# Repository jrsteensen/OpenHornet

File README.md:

# README
[TOC]

The OpenHornet Project is a F/A-18C OFP 13C Lot 20 1:1 Replica Simulator, consisting of a physical structure and electrical/software interfaces to a PC to be driven by Digital Combat Simulator (DCS).

* If you have any questions, visit our Discord server and ask questions. The Discord server will be an invaluable resource for you as your progress through the journey of your build.

### Looking for Software?
* [OpenHornet GitHub Software Repository](https://github.com/jrsteensen/OpenHornet-Software)

## Design Software Requirements
* Mechanical CAD Software Required: Fusion360
* Electrical CAD Software Required: KiCad 10
* Microsoft Office (or compatible)

## Contributing
[Want to contribute?](https://github.com/jrsteensen/OpenHornet/wiki/Contributing) Let's discuss what you want to work on in Discord or in an issue!

## References, Information, and How-Tos

### GitHub Repository File Structure
```
OpenHornet
├── .github (Contains issue templates, funding info, and GitHub actions.)
├── artwork (Subdivided into end items, contains stickers, placards, etc.)
├── ECAD (All PCBs and electrical design files. See folder README file for details.)
├── images (Contains images for use in the wiki or other OH documentation.)
├── reference (Contains reference models or geometry.)
├── release (Contains all files that makeup the release package. See folder README file for details.)
├── utils (Contains fonts or other similar required resources for development)
├── .gitignore (File that instructs the git repository to ignore certain file types.)
├── CODE_OF_CONDUCT.md (Our contributor code of conduct.)
├── CONTRIBUTING.md (Repository contribution and issue-reporting guidance.)
├── LICENSE.md (License file for the OpenHornet repository)
├── PULL_REQUEST_TEMPLATE.md (The repository pull request template.)
└── README.md (This file)
```

### Important Links
* [OpenHornet Start Here Page](https://openhornet.com/start-here/) - Seriously. Start here.
* [OpenHornet FAQ](https://openhornet.com/faq/) - You guessed it! The FAQ!
* [OpenHornet GitHub](https://github.com/jrsteensen/OpenHornet) - OpenHornet's GitHub repository for everything other than MCAD. Where you can find the latest under-development files.
* [OpenHornet Hardware Documentation](https://docs.openhornet.com/hardware/) - Generated hardware documentation, tutorials, and reference material.
* [OpenHornet Tutorials](https://github.com/jrsteensen/OpenHornet/tree/master/docs/tutorials) - Tutorials for OpenHornet.
* [OpenHornet Issues](https://github.com/jrsteensen/OpenHornet/issues) - Go here to file a bug, enhancement, obsolescence, or maintenance issue.
* [OpenHornet Authorized Vendors](https://openhornet.com/openhornet-authorized-vendors/) - These are vendors who are licensed to sell OpenHornet parts and assemblies. By purchasing from them, you also support OpenHornet as well!

### OpenHornet MCAD Model
These links will allow you to download a local copy of the OH MCAD model, for reference or so you can modify things for your personal pit. If you would like to contribute to the raw MCAD, talk to Noctum in the OH Discord. You will need to prove a basic level of proficiency and be known within the discord community before access will be granted.
> [!NOTE] 
> These links will download the latest & greatest (most likely in development and unstable) MCAD. Always verify fusion parts against release package manufacturing files prior to use, and they are used at the user's own risk.

* [Top Level](https://a360.co/3SuPQGs) - This is HUGE. Consider downloading individual consoles instead.
* [Upper Instrument Panel (UIP)](https://a360.co/3LHxMXd)
* [Lower Instrument Panel (LIP)](https://a360.co/3SbD7sc)
* [Left Console (LC)](https://a360.co/3dBR57I)
* [Right Console (RC)](https://a360.co/37pBiWj)
* [Center Tub (CT)](https://a360.co/3LKM3mc)

### Branches
* `master` branch is the stable release branch which represents the last release.
* `develop` is the latest working branch that will become the next release. It may or may not be functional as is.

## Authors and Acknowledgment

### Core Development Team
* Erik Scott (RandomTroubledMind): _Project Founder, Mechanical Design_ (Retired from OH)
* John Steensen (Noctum): _Co-Founder, Systems/Mechanical Design Lead_
* Oscar Arias (Amanuense): _Electrical/Software Design Lead_ (Retired from OH)

### Contributor Team
* Exprezzo
* Sandra
* Ben-F111
* Lazarus
* Russell
* Arribe VCAW-1
* Stang
* \[OCS\] CrazyCanuck
* Ulikaii

### Honorable Mentions
* __Logo Design__: NegativeONE
* __Development Builders/Testers__: Ajmilner,  Arribe VCAW-1, Ben-F111, BlaBlaCZ, bnepethomas, Dave the boss 918, DG, DotDotDotBH, Exprezzo, Higgins, Krikeee, Lazarus, Otso, Rampage2010, Russell, Sandra, Splash, Thib-O, tonyg, TripRodriguez, Yannick, 
* __Ultimate Supporters__: Sandra, Higgins, Chaps, [OCS] CrazyCanuck, Arribe VCAW-1, FL370Pilot, CorgiStyle, Swaney409, DenzilLee, ssgcline, Tyler | "Soapbox" - F-15E, RickH, AdamA, bob =), aesellars, Nick, PrivatePirate, Howling-Ape, papiplanes
* __Elite Supporters__: thib_o54, ChrisTiger#001, Nodar, Matt, Bill C, annerajb, Wargle T Eagle, Gnoni, Lefty, Reaper021, Murtle, gengispala, PatOPat, mattgw86, EinLama, Maddox, hunstone, Nodar, Ulukaii, Radek 41Sqn RAFAIR, mojito555
* __Donators__: AJMilner, bnepethomas, Carbine, Crosshairs, Exprezzo, Goutch, Higgins, hrnet940, hunstone, icemarkom, jcstreek, jkkicks, kika, Nik S, Rampage2010, Russell, Sandra, SrSosio, Swaney409, Tekadept + many more…
* __Inactive Dev Contributors__: Balz Reber (Balse), Magic_Man, Bullant, Gaberun24, Damien022, Baago, Caviar4, NegativeONE, Ravell
* **Subject Matter Expert**: FlyNavy75, Sixtigers, USMARINE108, Luft101, Lex

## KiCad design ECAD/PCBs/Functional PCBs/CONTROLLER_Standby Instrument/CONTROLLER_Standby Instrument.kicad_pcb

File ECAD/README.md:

* [OpenHornet Website](https://www.openhornet.com)
* [OpenHornet Discord](https://discord.gg/G5PA5ju)
* [Donate to OpenHornet](https://www.openhornet.com/donate.html)

# **ECAD DIRECTORY INFORMATION**

Engineering contributors and agents: start with the [ECAD design requirements framework](docs/requirements/README.md). AI-assisted contributors should also read the [Astra/Konnect/KiCad toolchain guide](docs/requirements/TOOLCHAIN.md). The framework distinguishes repository evidence, approved policy, unresolved decisions and hardware qualification states.

The purpose of this guide is to help enable the end-user to successfully accomplish the following:  
*   1:  Facilitate navigation of the file structure.
*   2:  Provide clarification regarding the manufacturing process of PCB's related to OpenHornet using JLCPCB.com
*   3:  How to install the current project KiCad baseline and set up libraries associated with OpenHornet. _(optional, required only if you wish to contribute.)_

 _Note:  Manufacturing files have been generated accordinging to JLCPCB.com guidelines.  If choosing a different PCB Manufacturer, make sure to research their formatting standards and modify the necessary manufacturing files accordingly. And if you choose to manufacture them yourself, best of luck!_

## **ECAD File Structure**

The ECAD Directory has been organized to facilitate the end user, regardless of skill or knowledge, in acquiring the necessary files needed to: 
* A: make adjustments to individual PCB's as needed using ECAD software (KiCad)
     * _and/or_
* B: submit an online order to have the PCB manufactured and assembled by a company.

**The structure of the ECAD Directory is summarized below:**

1. Within each labeled PCB folder, there will be a folder called "JLCPCB" and inside of that folder will be two additional folders called "gerbers" and "production_files"
2. **_All files you need for manufacturing are located in the "production_files" folder.  The gerbers are already compressed in a .zip file labeled the same way as the PCB folder their located in._** 
3. Additionally, there will be 2 .csv files:  _**BOM-'NAME OF PANEL'.csv**_ and  _**CPL-'NAME OF PANEL'.csv**_ that will contain a consolidated Bill of Materials (BOM) for components located on the top and bottom of the PCB, as well as the Control Panel File (CPL)  used for placing the components.

***PLEASE READ:  YOU NEED TO DOWNLOAD ALL 3 FILES WITHIN THE PRODUCTION_FILES FOLDER.  NOT JUST THE .ZIP.***

## **PCB Manufacturing**

At the moment, all manufacturing files have been standardized to allow for fabrication using JLC @ (https://www.jlcpcb.com).  You may use another PCB manufacturer of your choosing; however, you will be responsible for ensuring the required files meet specifications and formatting. 

***For details on the JLCPCB manufacturing process, please see the "MANUFACTURING.MD" located in the ECAD folder or CLICK THE LINK BELOW***

  [JLCPCB MANUFACTURING PROCESS & FAQ](MANUFACTURING.md)

## **Installation of KiCad and OpenHornet Libraries _(OPTIONAL)_**

*Installation of KiCad and OpenHornet Libraries is only required if you choose to contribute. See [CONTRIBUTING.md](../CONTRIBUTING.md) for more details.*

Before we begin, it is assumed that you have:
*  1:  Installed KiCad 10.x. The current validated AI-assisted reference environment uses KiCad 10.0.6; record and smoke-test newer versions before design mutation as described in [TOOLCHAIN.md](docs/requirements/TOOLCHAIN.md).
*  2:  Cloned the OpenHornet repository.

### STEP ONE:  Configure Paths & Create Environmental Variables

**Windows shortcut:** initialize KiCad 10 with its built-in libraries, then close KiCad and double-click [`Setup-OpenHornetKiCad.bat`](../utils/tools/ecad/Setup-OpenHornetKiCad.bat). The [complete setup script](docs/SYMBOL_LIBRARIES.md#windows-path-setup-script) configures all four paths, registers all six shared symbol libraries and `OH_Footprints`, and repairs existing shared entries in project library tables. It backs up every changed file and supports a preview with `-WhatIf`. After it succeeds, reopen KiCad; Steps One and Two below are the manual alternative.

Open up a new or previous project in KiCad.  For this example, I'll be using the MASTER ARM PANEL.  In the Top Menu: Navigate to Preferences --> Configure Paths

Create these four variables using absolute paths within your OpenHornet checkout:

| Variable | Repository folder |
| --- | --- |
| `KICAD_USER_OH_3DMODELS` | `ECAD/lib/OH_3DModels` |
| `KICAD_USER_OH_FOOTPRINTS` | `ECAD/lib` |
| `KICAD_USER_OH_SYMBOLS` | `ECAD/lib/OH_Symbols` |
| `KICAD_USER_OH_TEMPLATES` | `ECAD/lib/OH_Templates` |

The paths can be anywhere so long as they point to the OpenHornet checkout being edited. _Make sure the OH_FOOTPRINTS variable points to the `ECAD/lib` folder and **NOT** `ECAD/lib/OH_Footprints.pretty`._ If you use Git worktrees, do not let KiCad resolve libraries from a different checkout/revision than the PCB or schematic being edited.

### STEP TWO:  Add OpenHornet Symbol and Footprint Libraries

With the project window open, navigate to Preferences --> Manage Symbol Libraries.

In **Global Libraries**, add or edit the six shared libraries below. Use library format **KiCad** for each entry. The library paths use the variable configured above:

| Nickname | Library Path |
| --- | --- |
| `ABSIS` | `${KICAD_USER_OH_SYMBOLS}/ABSIS.kicad_sym` |
| `Arduino Pro Mini 5v` | `${KICAD_USER_OH_SYMBOLS}/Arduino Pro Mini 5v.kicad_sym` |
| `KiCadCustomLib` | `${KICAD_USER_OH_SYMBOLS}/KiCadCustomLib.kicad_symdir` |
| `OH_Interconnect` | `${KICAD_USER_OH_SYMBOLS}/OH_Interconnect.kicad_symdir` |
| `OH_Symbols` | `${KICAD_USER_OH_SYMBOLS}/OH_Symbols.kicad_symdir` |
| `OpenHornet` | `${KICAD_USER_OH_SYMBOLS}/OpenHornet.kicad_symdir` |

**Existing users:** change the paths for `OH_Symbols`, `KiCadCustomLib`, `OH_Interconnect` and `OpenHornet` from packed `.kicad_sym` files to their `.kicad_symdir` folders, using the exact nicknames in the table. Register each folder as one library, rather than adding its individual files. Check **Project Specific Libraries** for overriding entries with the same nicknames. `ABSIS` and `Arduino Pro Mini 5v` remain packed files.

Use the exact underscore nicknames `OH_Symbols` and `OH_Interconnect`, as shown in the table; do not substitute spaces. If a schematic still contains a library ID using a spaced nickname, correct its library reference through KiCad's symbol remapping tools. Changing a library-table nickname alone does not rewrite IDs embedded in schematics.

See [symbol library setup, Windows conversion and verification](docs/SYMBOL_LIBRARIES.md). Contributors pulling the converted folder only need to update their library mapping. The screenshots below illustrate the dialogs; use the paths in this table for KiCad 10.

Do the same thing for the footprint library, adding `ECAD/lib/OH_Footprints.pretty` with nickname `OH_Footprints`. The path should resolve as `${KICAD_USER_OH_FOOTPRINTS}/OH_Footprints.pretty`.

### STEP THREE:  Add ***KiCAD JLCPCB tools*** Plugin (Optional)
Bouni @ https://github.com/bouni/kicad-jlcpcb-tools has developed a plugin that allows you to search the JLCPCB parts database, assign LCSC article numbers to your parts, and generate production files for JLCPCB. This plugin is optional and is not a substitute for the OpenHornet sourcing/manufacturing requirements or the approved Astra/Konnect workflow.

*  1: Click **"Plugin and Content Manager"**
*  2: When the dialog box opens, click on **"Manage"**
*  3: When the **"Manage Repositories"** dialog box opens, Click the "+" sign and add the following:
    *  Name:  Bouni's KiCad repository
    *  URL:  https://raw.githubusercontent.com/Bouni/bouni-kicad-repository/main/repository.json
*  4: Once downloaded and installed, hit "Apply Changes"

### Congratulations. That's all you have to do for the shared OpenHornet library mapping.  The 3D models that are associated with the footprints will automatically be linked as long as the OH_Footprints are used.  

AI-assisted contributors should continue with [TOOLCHAIN.md](docs/requirements/TOOLCHAIN.md) before making hardware changes.

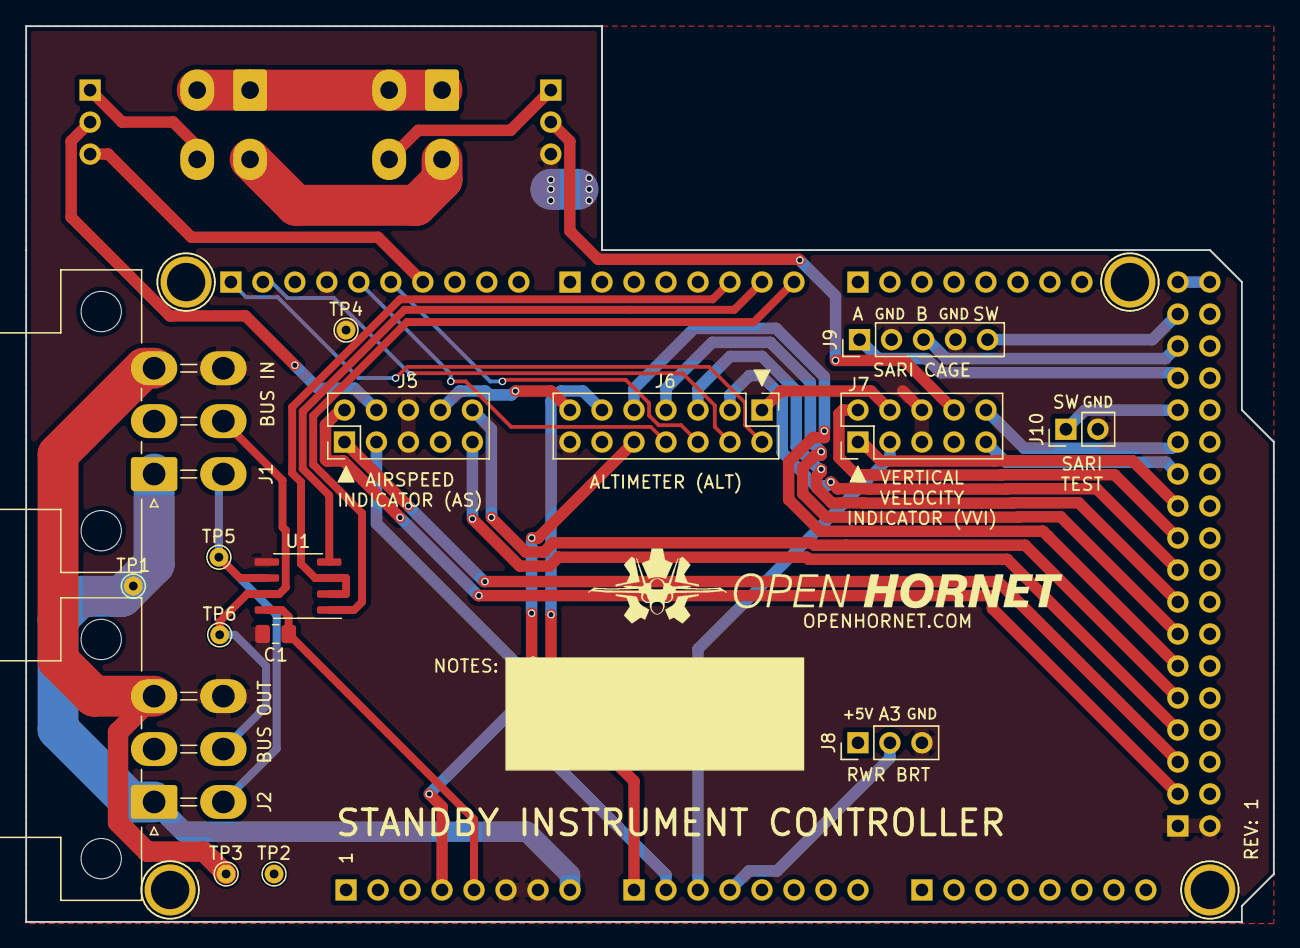
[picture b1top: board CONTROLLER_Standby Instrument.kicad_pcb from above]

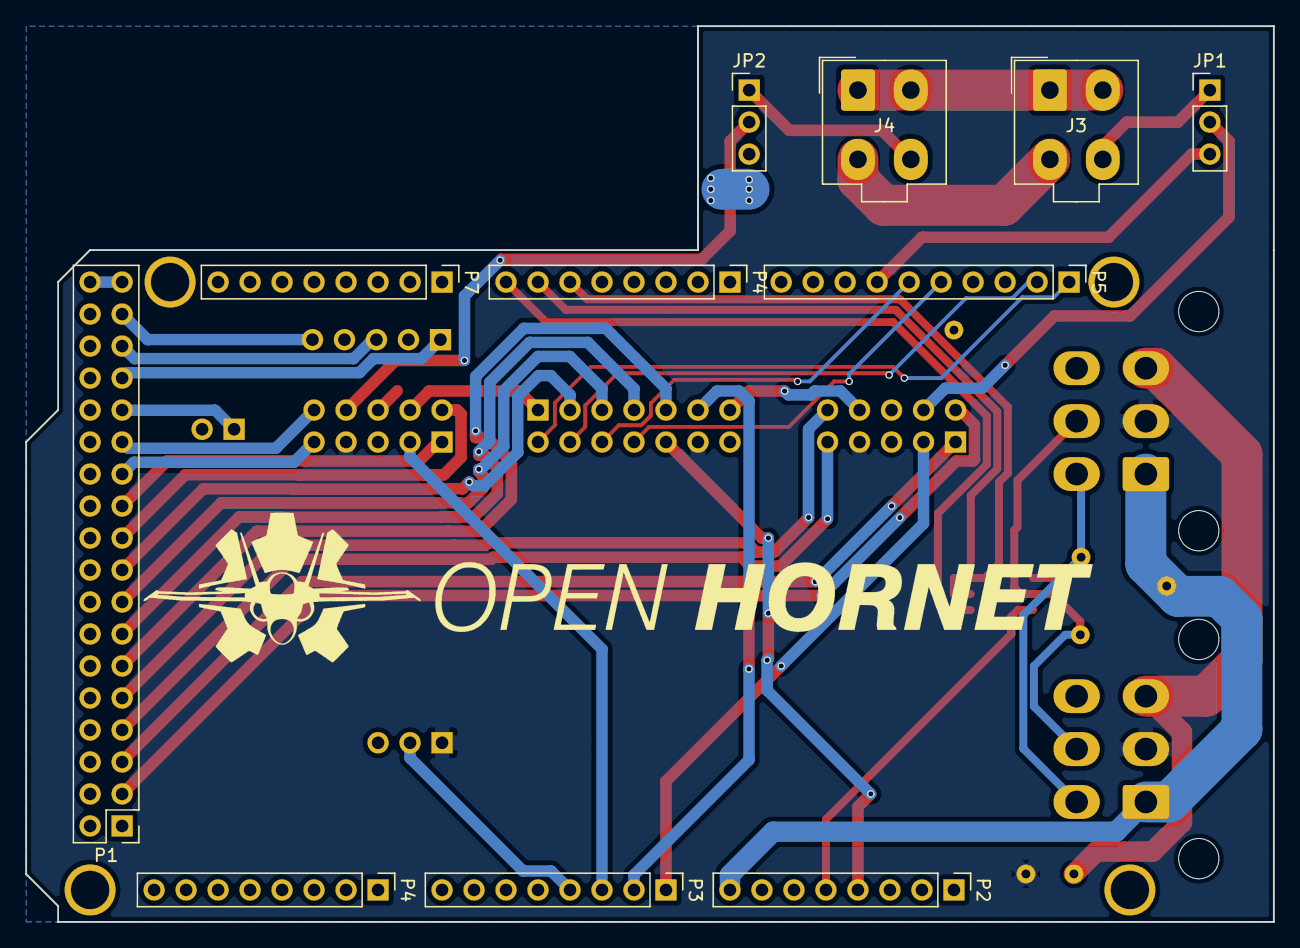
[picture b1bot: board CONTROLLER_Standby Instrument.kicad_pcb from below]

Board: 2 copper layers, 99.1 x 71.1 mm, 31 parts (11 on the bottom side), 45 nets.

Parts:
C1: 0.1uF; C_0805_2012Metric_Pad1.18x1.45mm_HandSolder
J1: BUS IN; Molex_Mini-Fit_Jr_5569-06A1_2x03_P4.20mm_Horizontal
J2: BUS OUT; Molex_Mini-Fit_Jr_5569-06A1_2x03_P4.20mm_Horizontal
J3: BL IN; Molex_Mini-Fit_Jr_5566-04A_2x02_P4.20mm_Vertical
J4: BL OUT; Molex_Mini-Fit_Jr_5566-04A_2x02_P4.20mm_Vertical
J5: AIRSPEED; PinHeader_2x05_P2.54mm_Vertical
J6: ALTIMETER; PinHeader_2x07_P2.54mm_Vertical
J7: VVI; PinHeader_2x05_P2.54mm_Vertical
J8: RWR_BRT; PinHeader_1x03_P2.54mm_Vertical
J9: SARI_CAGE; PinHeader_1x05_P2.54mm_Vertical
J10: SARI_TEST; PinHeader_1x02_P2.54mm_Vertical
JP1: BL_DIN_SEL; PinHeader_1x03_P2.54mm_Vertical
JP2: BL_DOUT_SEL; PinHeader_1x03_P2.54mm_Vertical
MK1, MK3, MK4, MK4#2: MH; Arduino_1pin
P1: Digital; PinHeader_2x18_P2.54mm_Vertical
P2: Power; PinHeader_1x08_P2.54mm_Vertical
P3, P4: Analog; PinHeader_1x08_P2.54mm_Vertical
P4#2: PWM; PinHeader_1x08_P2.54mm_Vertical
P5: PWM; PinHeader_1x10_P2.54mm_Vertical
P7: Communication; PinHeader_1x08_P2.54mm_Vertical
TP1: TP-12; TestPoint_THTPad_D1.5mm_Drill0.7mm
TP2: TP-5V; TestPoint_THTPad_D1.5mm_Drill0.7mm
TP3: TP-3.3V; TestPoint_THTPad_D1.5mm_Drill0.7mm
TP4: TP-GND; TestPoint_THTPad_D1.5mm_Drill0.7mm
TP5: TP-A; TestPoint_THTPad_D1.5mm_Drill0.7mm
TP6: TP-B; TestPoint_THTPad_D1.5mm_Drill0.7mm
U1: MAX487EESA+T; SOIC-8_3.9x4.9mm_P1.27mm

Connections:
+3V3: J6.10, P2.4
+5V: C1.1, P2.5, U1.8
+5VD: P1.35, P1.36
/0(Rx0): P4#2.8, U1.1
/1(Tx0): P4#2.7, U1.4
/2(**): P4#2.6, U1.2, U1.3
/11(**): JP1.3, P5.7
/12(**): J6.6, P5.6
/13(**): J6.8, P5.5
/22: J9.5, P1.33
/24: J9.3, P1.31
/26: J9.1, P1.29
/28: J10.1, P1.27
/30: J7.10, P1.25
/32: J7.9, P1.23
/34: J7.1, P1.21
/36: J7.2, P1.19
/38: J6.3, P1.17
/40: J6.5, P1.15
/42: J6.7, P1.13
/44: J6.9, P1.11
/46: J5.10, P1.9
/48: J5.9, P1.7
/50(MISO): J5.1, P1.5
/52(SCK): J5.2, P1.3
/+3.3V_SUPPLY: J1.3, J2.3, TP3.1
/+5V_SUPPLY: J1.2, J2.2, J5.7, J6.12, J7.7, J8.1, TP2.1
/+12V_SUPPLY: J1.1, J2.1, P2.8, TP1.1
/A0: J5.3, P3.1
/A1: J6.11, P3.2
/A2: J7.3, P3.3
/A3: J8.2, P3.4
/BUS-A: J1.4, J2.4, TP5.1, U1.6
/BUS-B: J1.5, J2.5, TP6.1, U1.7
/DATAIN: J3.4, JP1.1
/DATAOUT: J4.4, JP2.1
/LED+5V: J3.1, J3.2, J4.1, J4.2
/LEDGND: J3.3, J4.3
/LED_DIN: J5.4, JP1.2
/LED_DOUT: J7.8, JP2.2
/LED_DOUT1: J5.8, J6.13
/LED_DOUT2: J6.1, J7.4
/SCL: J6.2, P5.1
/SDA: J6.4, P5.2
GND: C1.2, J1.6, J2.6, J5.5, J5.6, J6.14, J7.5, J7.6, J8.3, J9.2, J9.4, J10.2, JP2.3, P1.1, P1.2, P2.6, P2.7, P5.4, TP4.1, U1.5

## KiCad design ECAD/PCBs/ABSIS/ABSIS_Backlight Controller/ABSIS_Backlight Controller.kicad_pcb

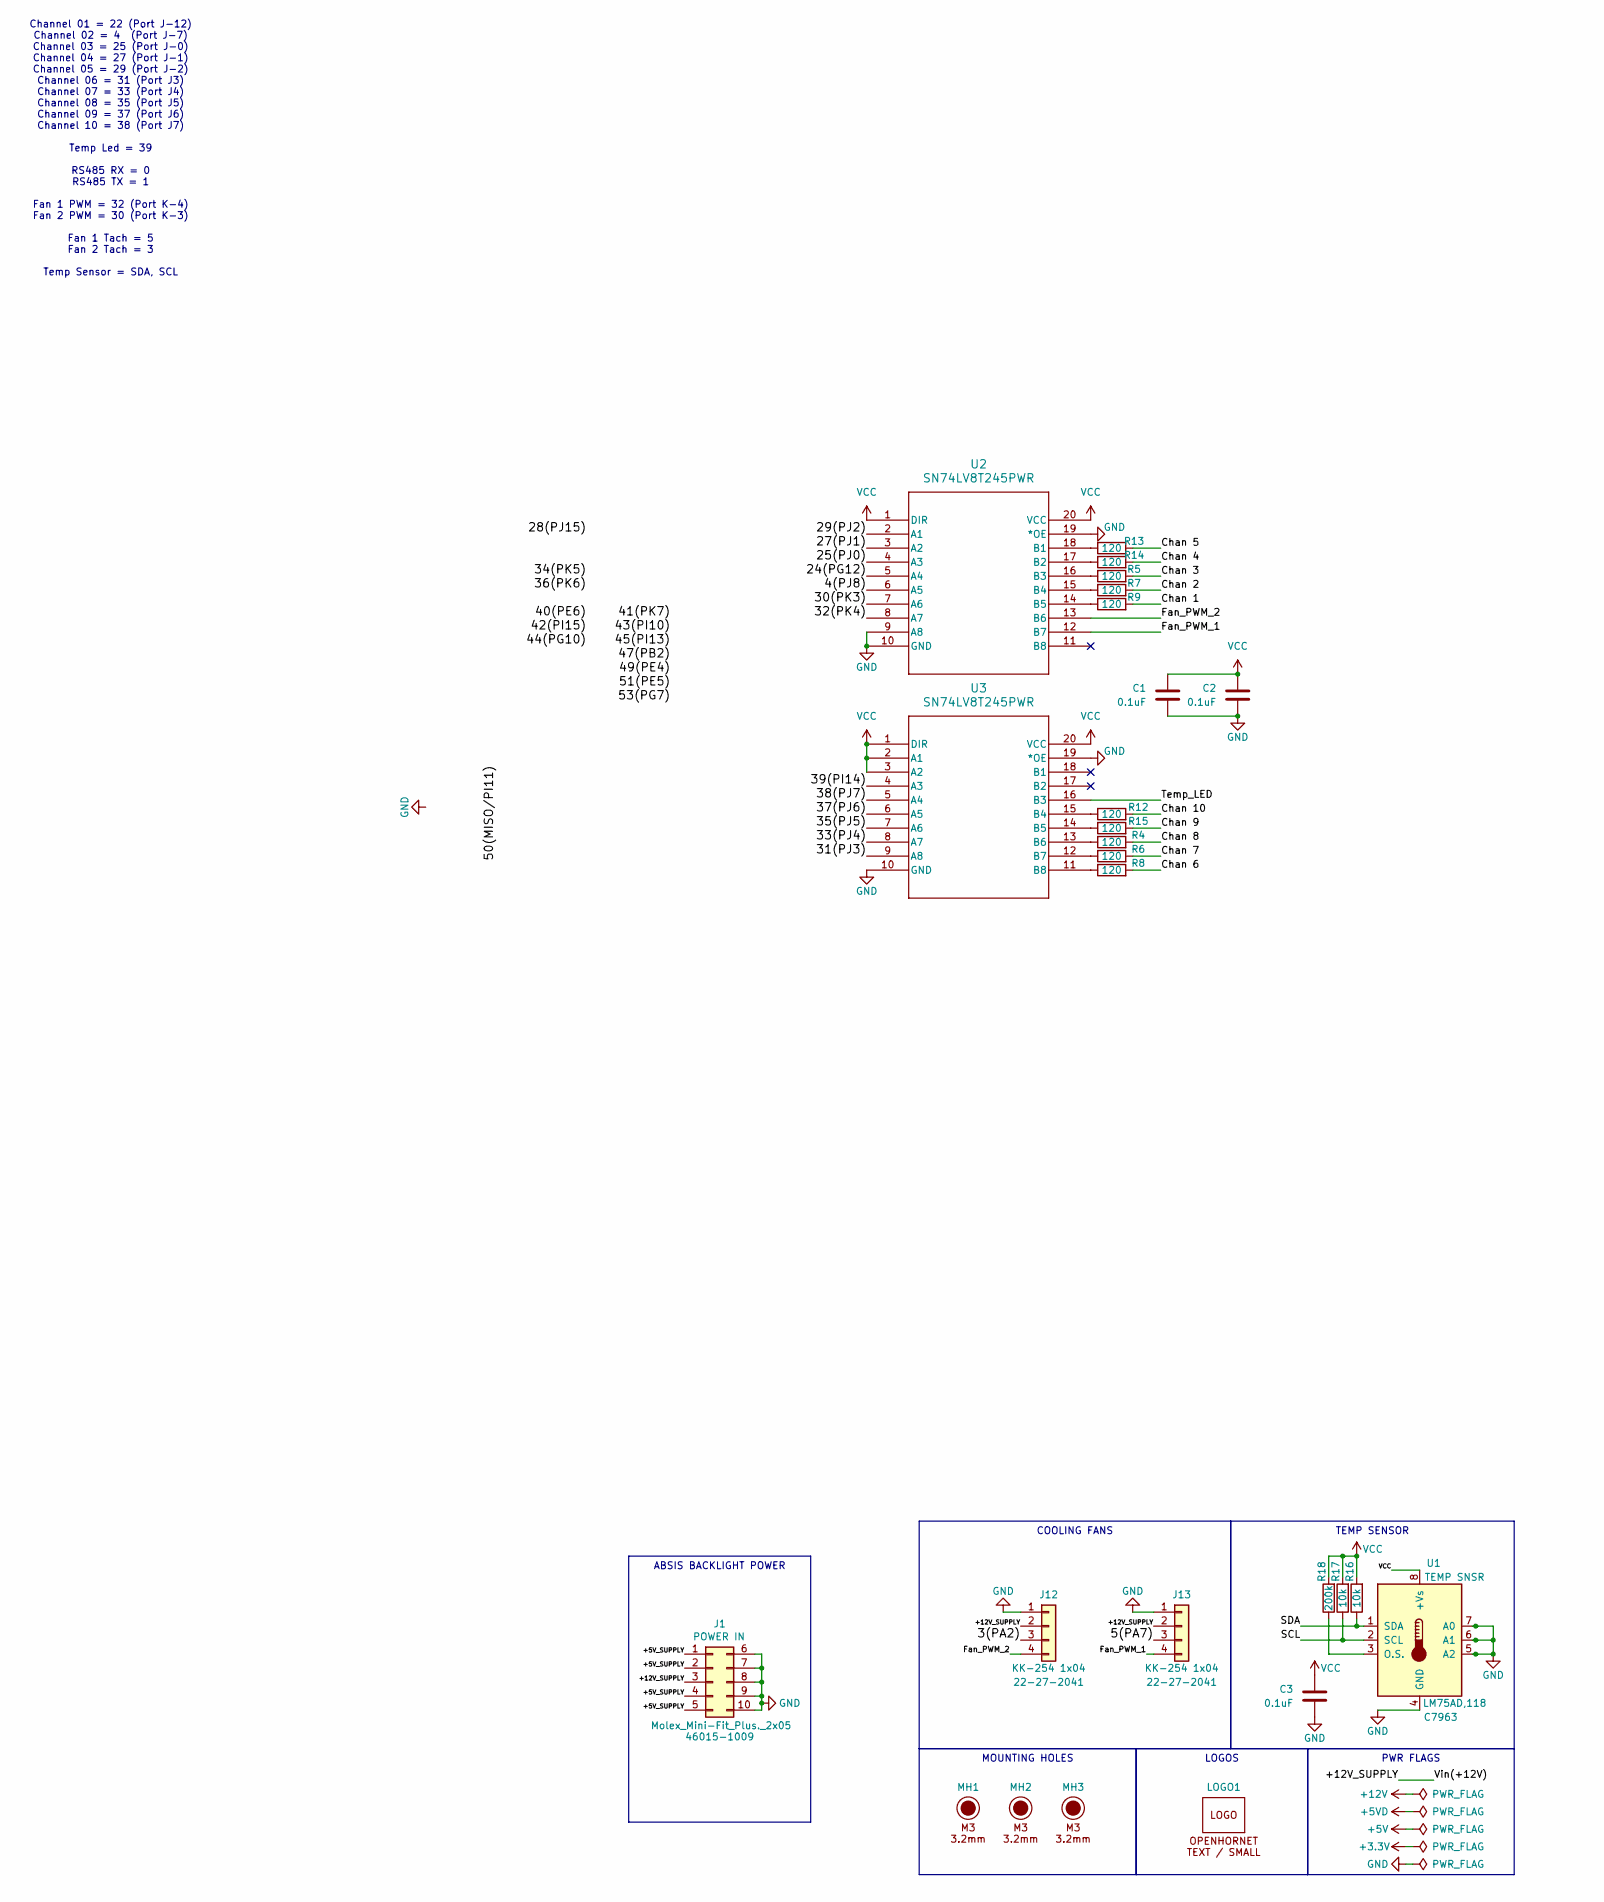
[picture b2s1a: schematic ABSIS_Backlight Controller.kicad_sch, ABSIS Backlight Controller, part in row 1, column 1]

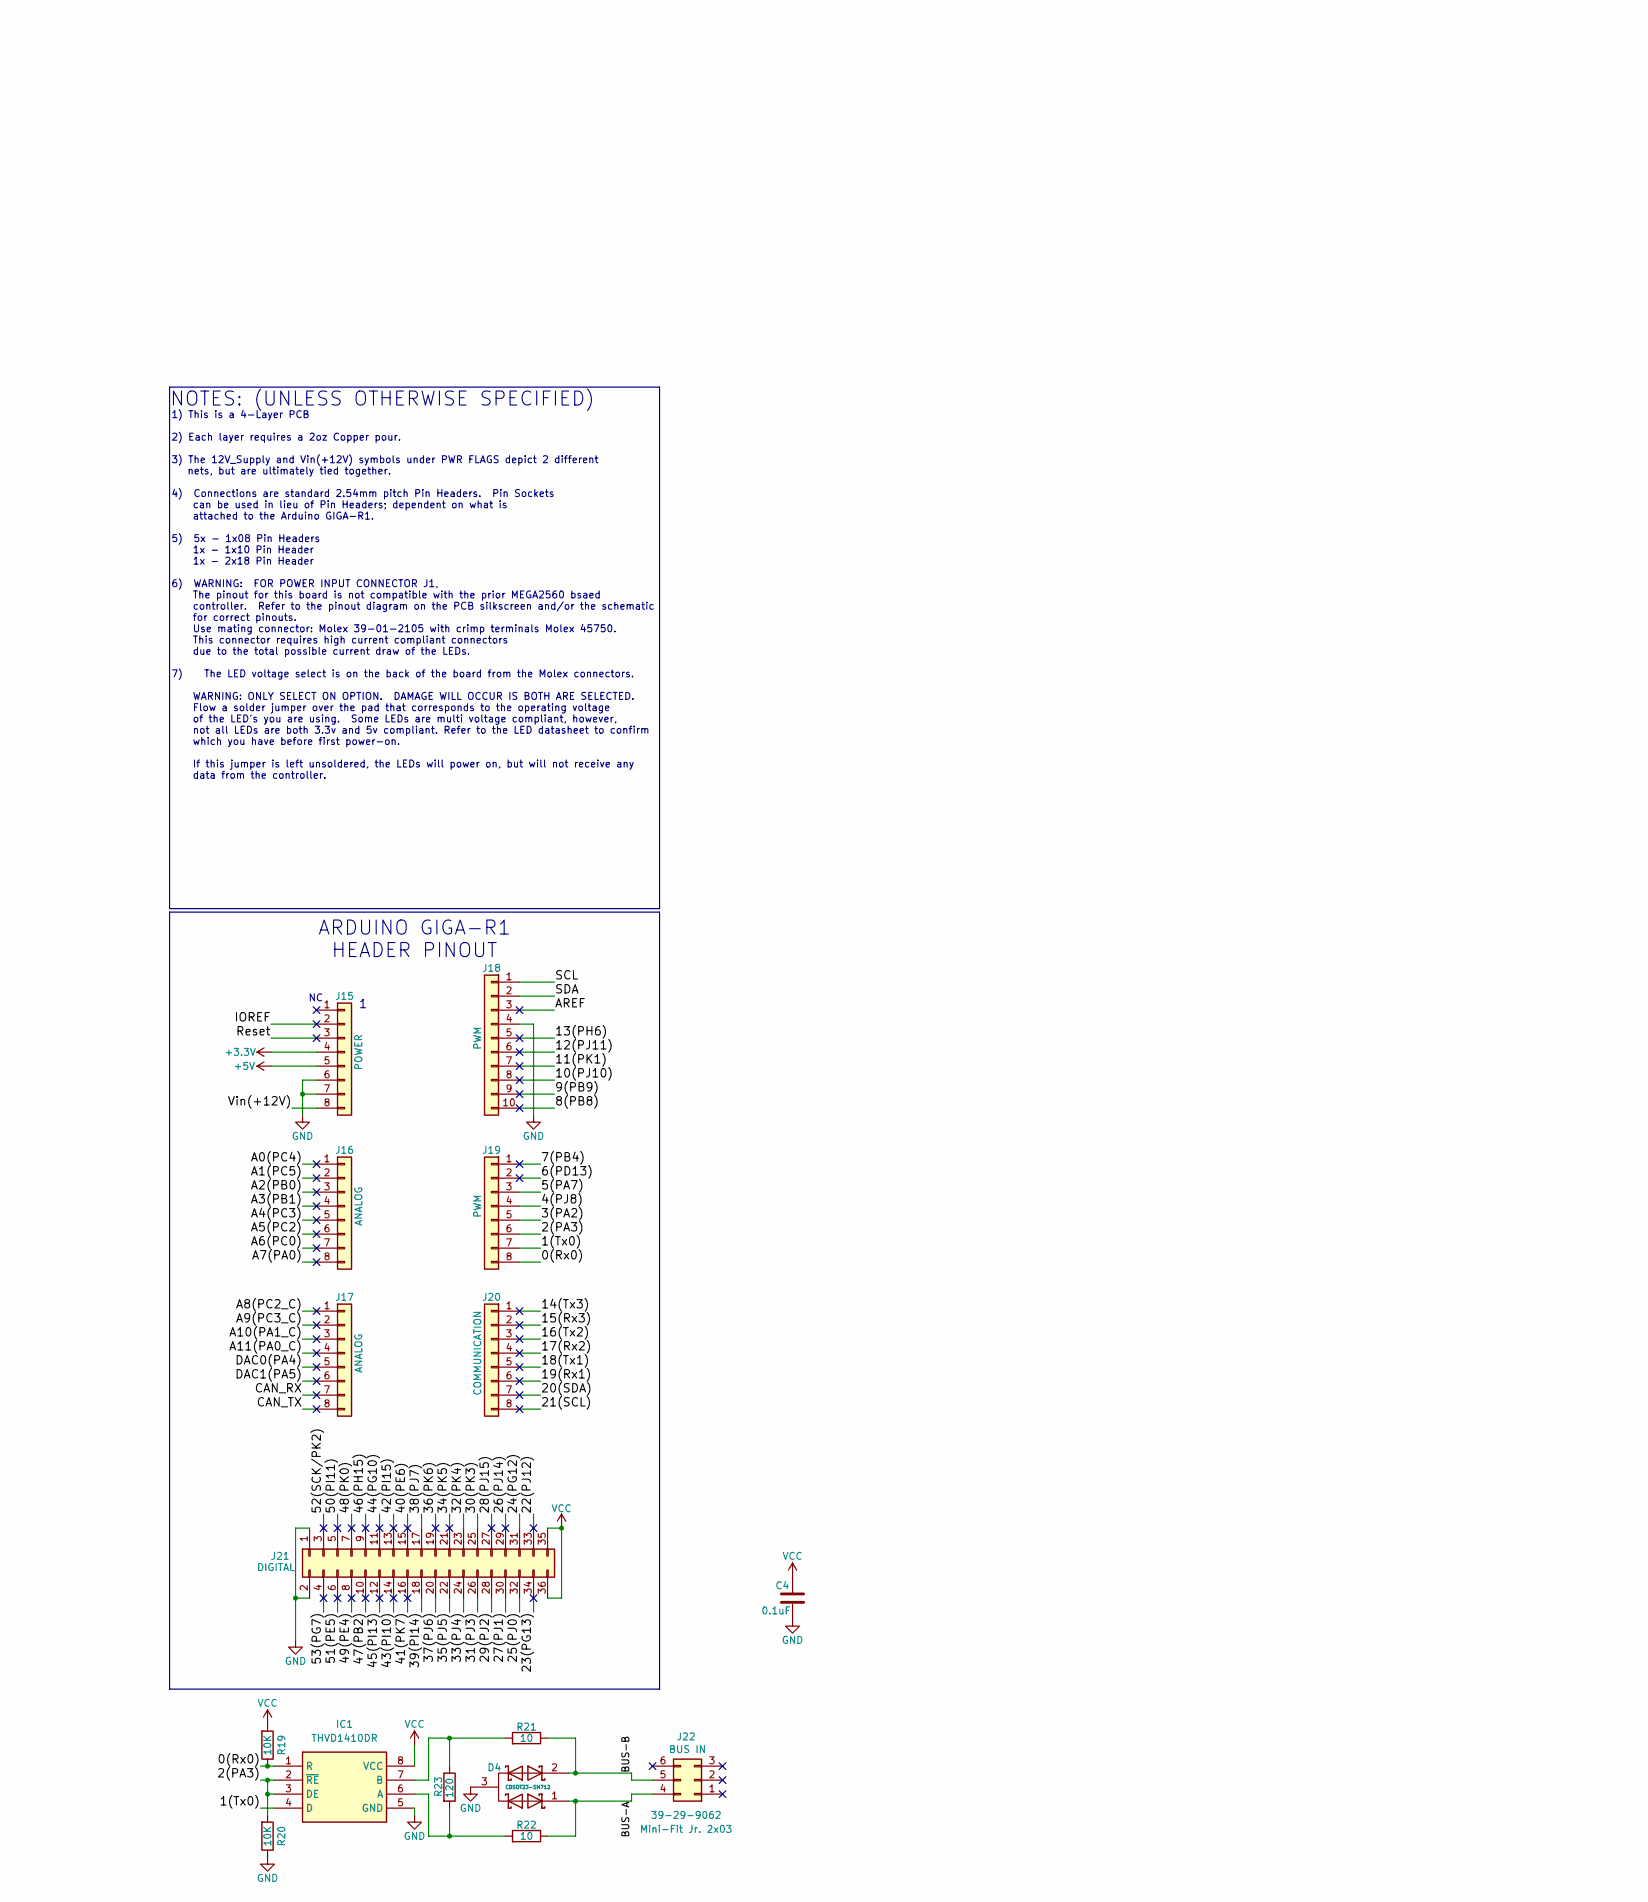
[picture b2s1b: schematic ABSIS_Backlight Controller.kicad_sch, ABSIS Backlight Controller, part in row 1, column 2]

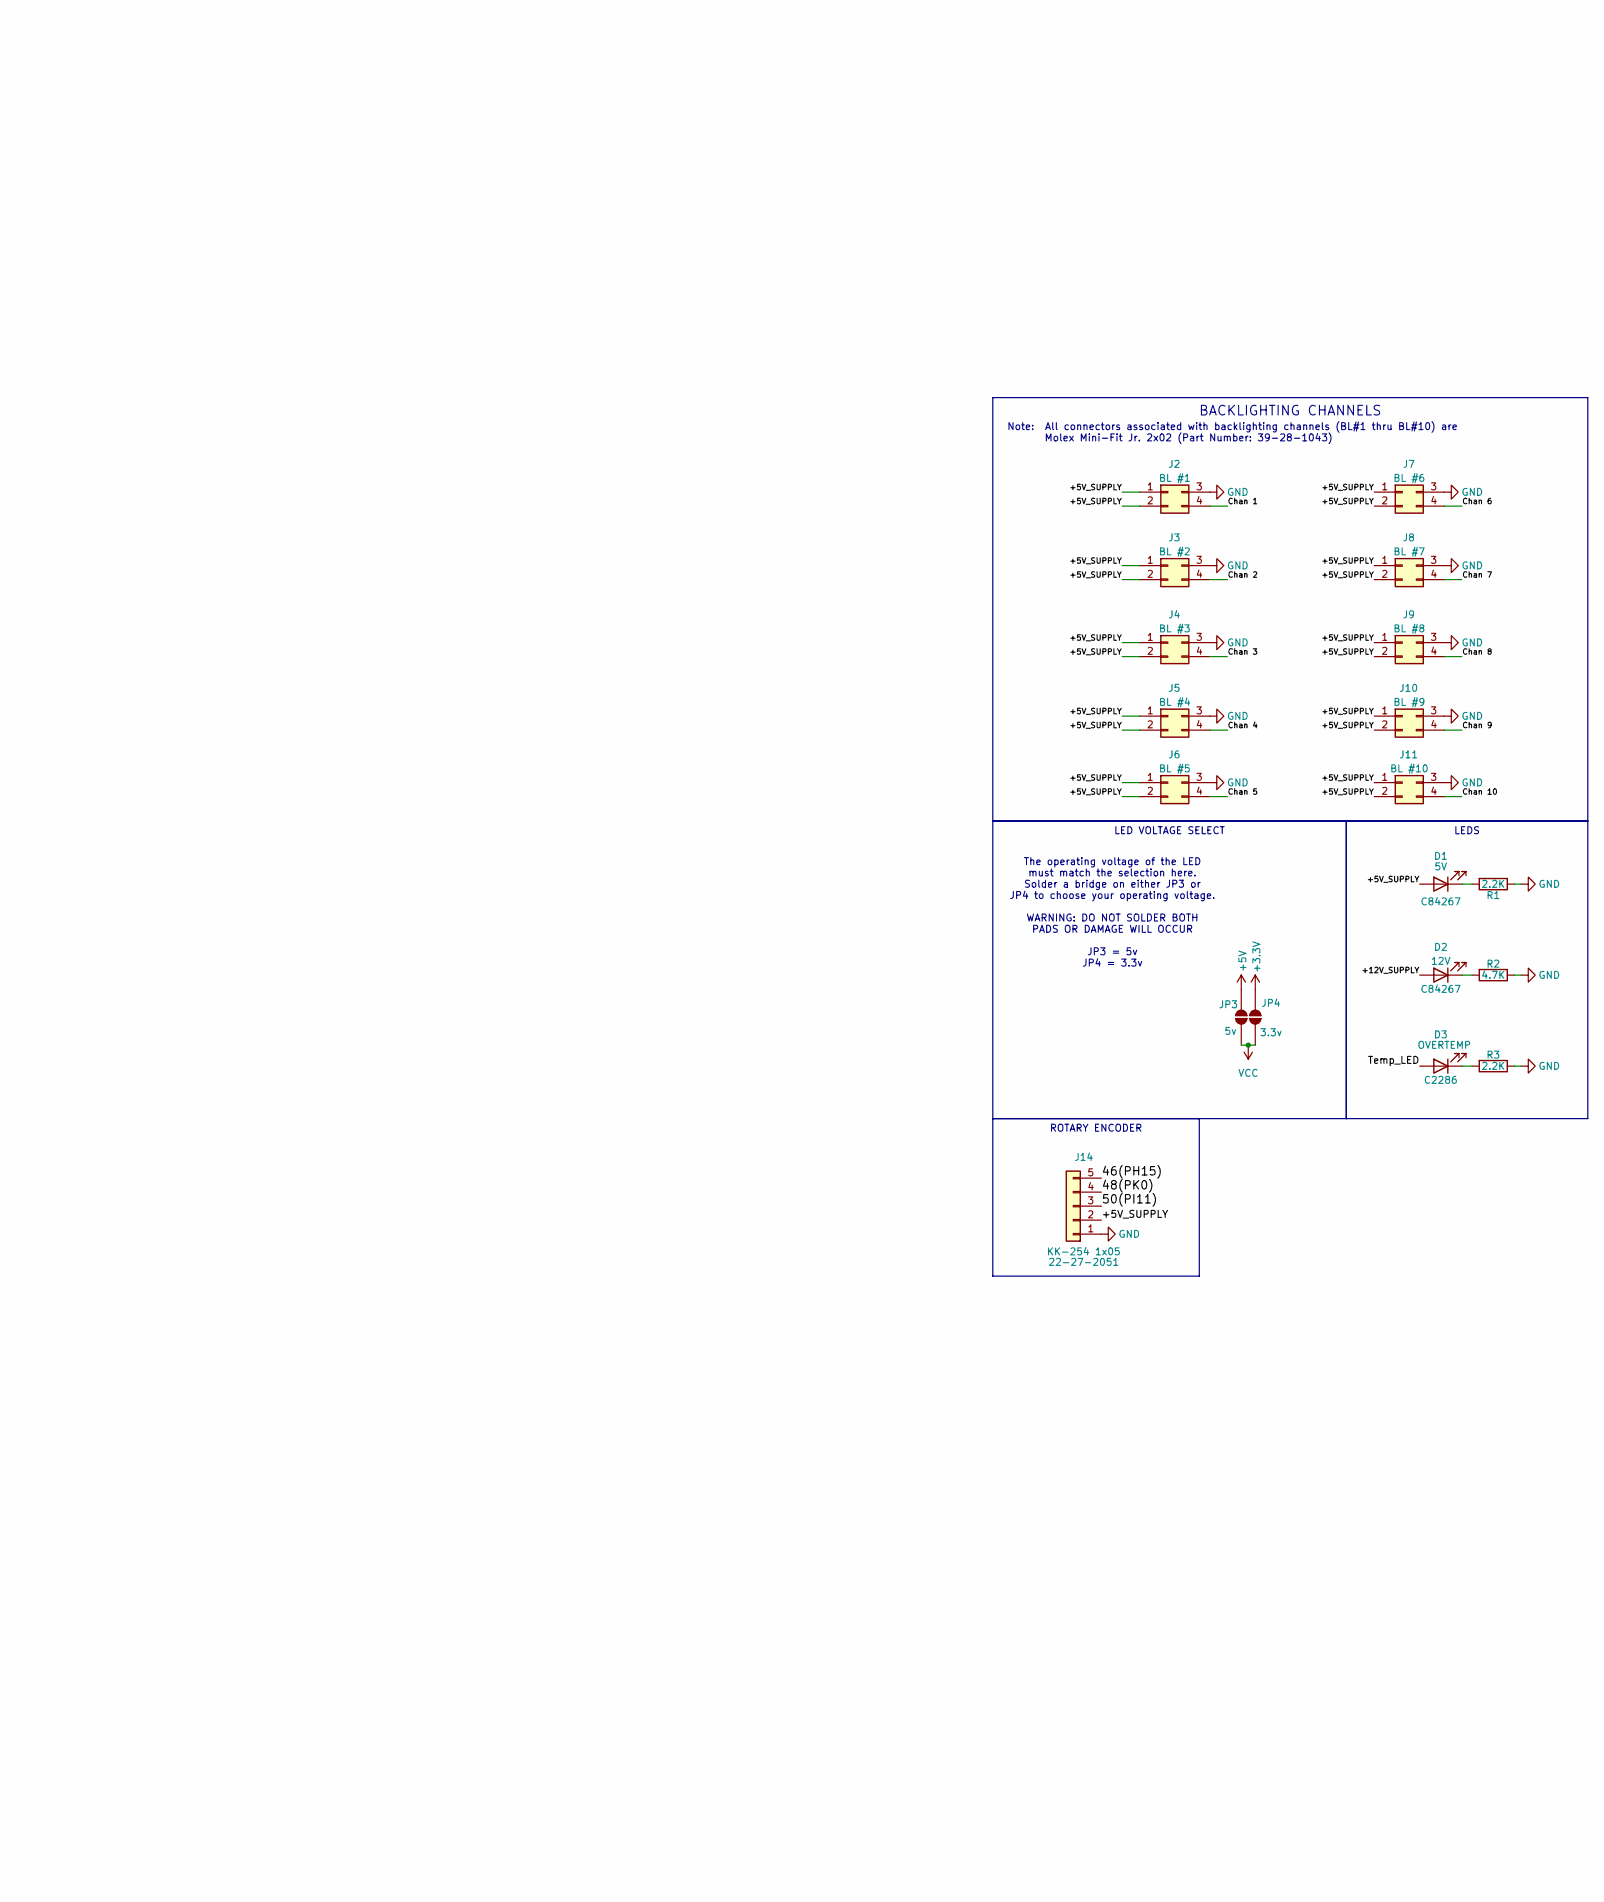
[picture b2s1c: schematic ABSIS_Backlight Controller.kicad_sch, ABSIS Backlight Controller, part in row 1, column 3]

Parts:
C1, C2, C3, C4: 0.1uF; C_0603_1608Metric; Manufacturer PN CC0603KRX7R9BB104; LCSC C14663
D1, D2: Green; LED_0603_1608Metric_Pad1.05x0.95mm_HandSolder; Manufacturer PN NCD0603G1; LCSC C84267
D3: Red; LED_0603_1608Metric_Pad1.05x0.95mm_HandSolder; Manufacturer PN KT-0603R; LCSC C2286
D4: CDSOT23-SM712; Manufacturer_Part_Number CDSOT23-SM712; Mouser Part Number 652-CDSOT23-SM712
IC1: THVD1410DR; Manufacturer_Part_Number THVD1410DR; Mouser Part Number 595-THVD1410DR
J1: Molex_Mini-Fit_Plus._2x05; Molex_Mini-Fit_Jr_5566-10A2_2x05_P4.20mm_Vertical; Manufacturer PN 46015-1009; LCSC C587474
J2, J3, J4, J5, J6, J7, J8, J9, J10, J11: Mini-Fit Jr. 2x02; Molex_Mini-Fit_Jr_5566-04A_2x02_P4.20mm_Vertical; Manufacturer PN 39-28-1043; LCSC C293502
J12, J13: KK-254 1x04; Molex_KK-254_AE-6410-04A_1x04_P2.54mm_Vertical; Manufacturer PN 22-27-2041; LCSC C504991
J14: KK-254 1x05; Molex_KK-254_AE-6410-05A_1x05_P2.54mm_Vertical; Manufacturer PN 22-27-2051; LCSC C585785
J15, J16, J17, J19, J20: PinHeader_1x08; PinHeader_1x08_P2.54mm_Vertical; Manufacturer PN PH1-08-UA
J18: PinHeader_1x10; PinHeader_1x10_P2.54mm_Vertical; Manufacturer PN PH1-10-UA
J21: PinHeader_2x18; PinHeader_2x18_P2.54mm_Vertical; Manufacturer PN PH2-18-UA
J22: Mini-Fit Jr. 2x03; Molex_Mini-Fit_Jr_5566-06A2_2x03_P4.20mm_Vertical; Manufacturer PN 39-29-9062; LCSC C505177
JP3: 5v; SolderJumper-2_P1.3mm_Open_RoundedPad1.0x1.5mm
JP4: 3.3v; SolderJumper-2_P1.3mm_Open_RoundedPad1.0x1.5mm
LOGO1: LOGO; LOGO_OH_Text_Small
MH1, MH2, MH3: M3 / 3.2mm; MountingHole_3.2mm_M3_DIN965
R1, R3: 2.2K; R_0603_1608Metric; Manufacturer PN 0603WAF2201T5E; LCSC C4190
R2: 4.7K; R_0603_1608Metric; Manufacturer PN 0603WAF4701T5E; LCSC C23162
R4, R5, R6, R7, R8, R9, R12, R13, R14, R15, R23: 120; R_0603_1608Metric; Manufacturer PN 0603WAF1200T5E; LCSC C22787
R16, R17: 10k; R_0603_1608Metric; Manufacturer PN 0603WAF1002T5E; LCSC C25804
R18: 200k; R_0603_1608Metric; Manufacturer PN 0603WAF2201T5E; LCSC C25811
R19, R20: 10K; R_0603_1608Metric_Pad0.98x0.95mm_HandSolder; LCSC C25804
R21, R22: 10; R_0603_1608Metric_Pad0.98x0.95mm_HandSolder; LCSC C844519
U1: LM75AD,118; SOIC-8_3.9x4.9mm_P1.27mm; Manufacturer PN LM75AD,118; LCSC C7963
U2, U3: SN74LV8T245PWR; TSSOP20_PW_TEX; LCSC C20345798

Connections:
+3.3V: J15.4, JP4.2 (B)
+5V: J15.5, JP3.2 (B)
/0(Rx0): IC1.1 (R), J19.8, R19.1
/1(Tx0): IC1.4 (D), J19.7
/2(PA3): IC1.2 (~RE), IC1.3 (DE), J19.6, R20.2
/3(PA2): J12.3, J19.5
/4(PJ8): J19.4, U2.6 (A5)
/5(PA7): J13.3, J19.3
/6(PD13): J19.2
/7(PB4): J19.1
/8(PB8): J18.10
/9(PB9): J18.9
/10(PJ10): J18.8
/11(PK1): J18.7
/12(PJ11): J18.6
/13(PH6): J18.5
/14(Tx3): J20.1
/15(Rx3): J20.2
/16(Tx2): J20.3
/17(Rx2): J20.4
/18(Tx1): J20.5
/19(Rx1): J20.6
/20(SDA): J20.7
/21(SCL): J20.8
/22(PJ12): J21.33
/23(PG13): J21.34
/24(PG12): J21.31, U2.5 (A4)
/25(PJ0): J21.32, U2.4 (A3)
/26(PJ14): J21.29
/27(PJ1): J21.30, U2.3 (A2)
/28(PJ15): J21.27
/29(PJ2): J21.28, U2.2 (A1)
/30(PK3): J21.25, U2.7 (A6)
/31(PJ3): J21.26, U3.9 (A8)
/32(PK4): J21.23, U2.8 (A7)
/33(PJ4): J21.24, U3.8 (A7)
/34(PK5): J21.21
/35(PJ5): J21.22, U3.7 (A6)
/36(PK6): J21.19
/37(PJ6): J21.20, U3.6 (A5)
/38(PJ7): J21.17, U3.5 (A4)
/39(PI14): J21.18, U3.4 (A3)
/40(PE6): J21.15
/41(PK7): J21.16
/42(PI15): J21.13
/43(PI10): J21.14
/44(PG10): J21.11
/45(PI13): J21.12
/46(PH15): J14.5, J21.9
/47(PB2): J21.10
/48(PK0): J14.4, J21.7
/49(PE4): J21.8
/50(PI11): J14.3, J21.5
/51(PE5): J21.6
/52(SCK/PK2): J21.3
/53(PG7): J21.4
/A0(PC4): J16.1
/A1(PC5): J16.2
/A2(PB0): J16.3
/A3(PB1): J16.4
/A4(PC3): J16.5
/A5(PC2): J16.6
/A6(PC0): J16.7
/A7(PA0): J16.8
/A8(PC2_C): J17.1
/A9(PC3_C): J17.2
/A10(PA1_C): J17.3
/A11(PA0_C): J17.4
/AREF: J18.3
/BUS-A: D4.1, J22.4, R22.2
/BUS-B: D4.2, J22.5, R21.2
/CAN_RX: J17.7
/CAN_TX: J17.8
/Chan 1: J2.4, R9.2
/Chan 2: J3.4, R7.2
/Chan 3: J4.4, R5.2
/Chan 4: J5.4, R14.2
/Chan 5: J6.4, R13.2
/Chan 6: J7.4, R8.2
/Chan 7: J8.4, R6.2
/Chan 8: J9.4, R4.2
/Chan 9: J10.4, R15.2
/Chan 10: J11.4, R12.2
/DAC0(PA4): J17.5
/DAC1(PA5): J17.6
/Fan_PWM_1: J13.4, U2.12 (B7)
/Fan_PWM_2: J12.4, U2.13 (B6)
/IOREF: J15.2
/Reset: J15.3
/SCL: J18.1, R17.1, U1.2 (SCL)
/SDA: J18.2, R16.1, U1.1 (SDA)
/Temp_LED: D3.2 (A), U3.16 (B3)
GND: C1.2, C2.2, C3.2, C4.1, D4.3, IC1.5 (GND), J1.6, J1.7, J1.8, J1.9, J1.10, J2.3 (Pin_2), J3.3 (Pin_2), J4.3 (Pin_2), J5.3 (Pin_2), J6.3 (Pin_2), J7.3 (Pin_2), J8.3 (Pin_2), J9.3 (Pin_2), J10.3 (Pin_2), J11.3 (Pin_2), J12.1, J13.1, J14.1, J15.6, J15.7, J18.4, J21.1, J21.2, R1.1, R2.1, R3.1, R20.1, U1.4 (GND), U1.5 (A2), U1.6 (A1), U1.7 (A0), U2.9 (A8), U2.10 (GND), U2.19 (*OE), U3.10 (GND), U3.19 (*OE)
unnamed: D1.1 (K), R1.2
unnamed: D2.1 (K), R2.2
unnamed: D3.1 (K), R3.2
unnamed: IC1.6 (A), R22.1, R23.1
unnamed: IC1.7 (B), R21.1, R23.2
unnamed: R18.1, U1.3 (O.S.)
unnamed: R13.1, U2.18 (B1)
unnamed: R14.1, U2.17 (B2)
unnamed: R5.1, U2.16 (B3)
unnamed: R7.1, U2.15 (B4)
unnamed: R9.1, U2.14 (B5)
unnamed: R12.1, U3.15 (B4)
unnamed: R15.1, U3.14 (B5)
unnamed: R4.1, U3.13 (B6)
unnamed: R6.1, U3.12 (B7)
unnamed: R8.1, U3.11 (B8)
VCC: C1.1, C2.1, C3.1, C4.2, IC1.8 (VCC), J21.35, J21.36, JP3.1 (A), JP4.1 (A), R16.2, R17.2, R18.2, R19.2, U1.8 (+Vs), U2.1 (DIR), U2.20 (VCC), U3.1 (DIR), U3.2 (A1), U3.3 (A2), U3.20 (VCC)

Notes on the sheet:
The operating voltage of the LED must match the selection here. Solder a bridge on either JP3 or JP4 to choose your operating voltage. WARNING: DO NOT SOLDER BOTH PADS OR DAMAGE WILL OCCUR JP3 = 5v JP4 = 3.3v
1) This is a 4-Layer PCB 2) Each layer requires a 2oz Copper pour. 3) The 12V_Supply and Vin(+12V) symbols under PWR FLAGS depict 2 different nets, but are ultimately tied together. 4) Connections are standard 2.54mm pitch Pin Headers. Pin Sockets can be used in lieu of Pin Headers; dependent on wh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
Note: All connectors associated with backlighting channels (BL#1 thru BL#10) are Molex Mini-Fit Jr. 2x02 (Part Number: 39-28-1043)
Channel 01 = 22 (Port J-12) Channel 02 = 4 (Port J-7) Channel 03 = 25 (Port J-0) Channel 04 = 27 (Port J-1) Channel 05 = 29 (Port J-2) Channel 06 = 31 (Port J3) Channel 07 = 33 (Port J4) Channel 08 = 35 (Port J5) Channel 09 = 37 (Port J6) Channel 10 = 38 (Port J7) Temp Led = 39 RS485 RX = 0 RS485 T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
NOTES: (UNLESS OTHERWISE SPECIFIED)
LEDS
BACKLIGHTING CHANNELS
ABSIS BACKLIGHT POWER
ROTARY ENCODER
TEMP SENSOR
PWR FLAGS
COOLING FANS
LOGOS
MOUNTING HOLES
ARDUINO GIGA-R1 HEADER PINOUT
LED VOLTAGE SELECT

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
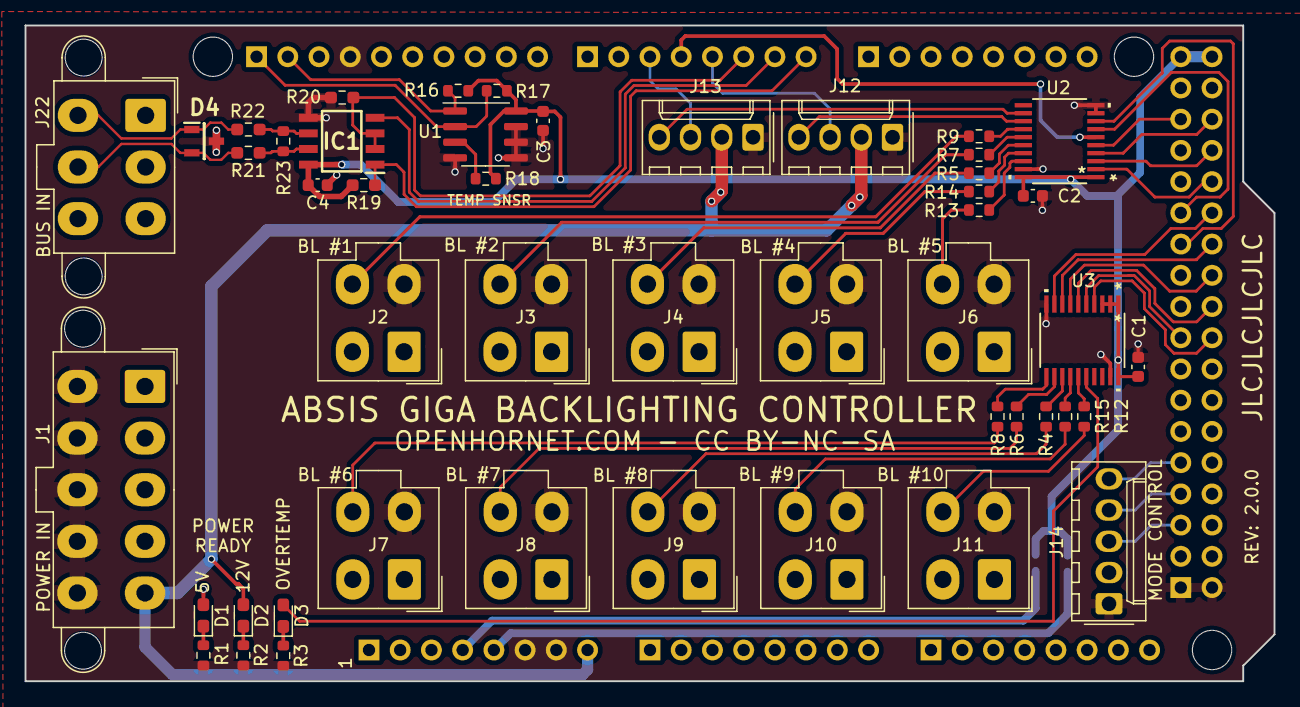
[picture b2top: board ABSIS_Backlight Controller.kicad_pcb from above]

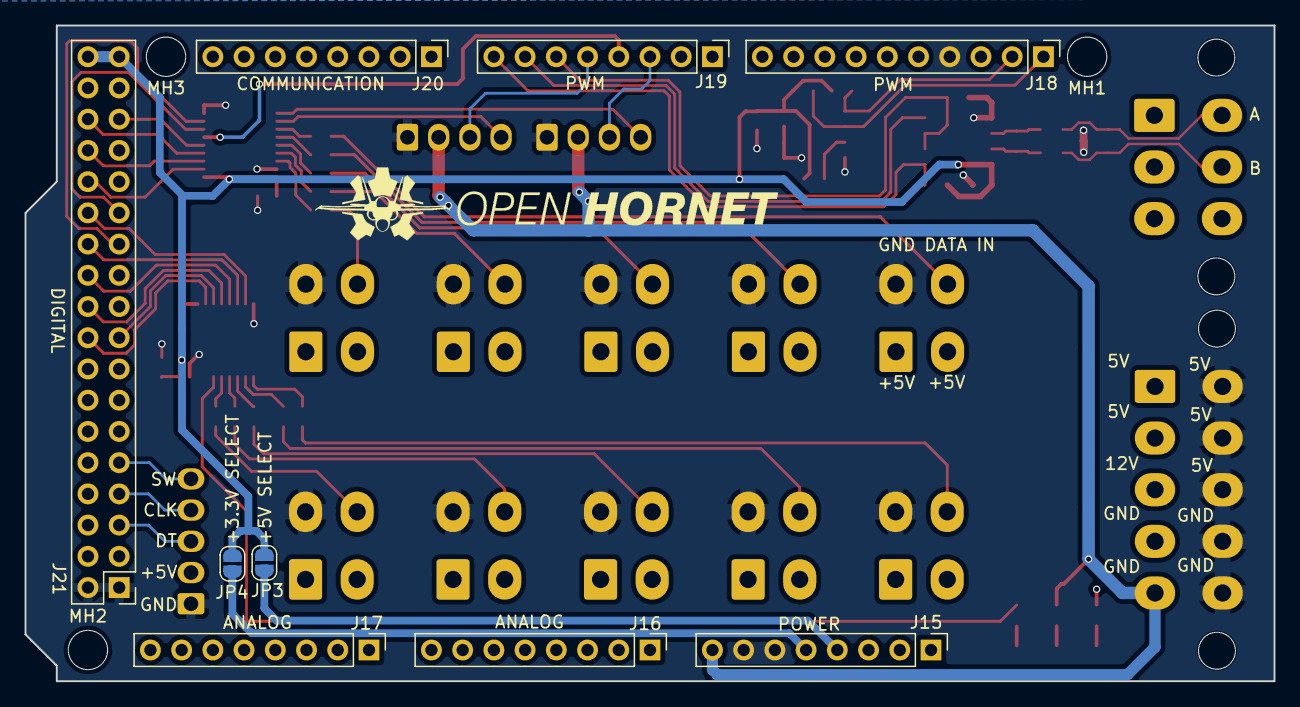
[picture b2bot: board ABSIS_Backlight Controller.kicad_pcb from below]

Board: 4 copper layers, 101.6 x 53.3 mm, 61 parts (13 on the bottom side), 60 nets.

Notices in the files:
ECAD/PCBs/ABSIS/ABSIS_ALE+/ABSIS ALE+.kicad_pcb:
License:  CC BY-NC-SA
OPENHORNET.COM - CC BY-NC-SA - REV: ${REVISION}
ECAD/PCBs/Functional PCBs/CONTROLLER_AMPCD DDI/CONTROLLER_AMPCD DDI.kicad_pcb:
CC BY-NC-SA
ECAD/PCBs/Functional PCBs/CONTROLLER_Radar Altimeter/CONTROLLER_Radar Altimeter.kicad_pcb:
CC BY-NC-SA - REV: 5
README.md:
License: BY-NC-SA 4.0
